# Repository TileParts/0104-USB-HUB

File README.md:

0104-USB-HUB
==========

一个带分控开关的一拖三 USB 2.0 Hub。

## 协议

[CERN-OHL-P-2.0](LICENSE)

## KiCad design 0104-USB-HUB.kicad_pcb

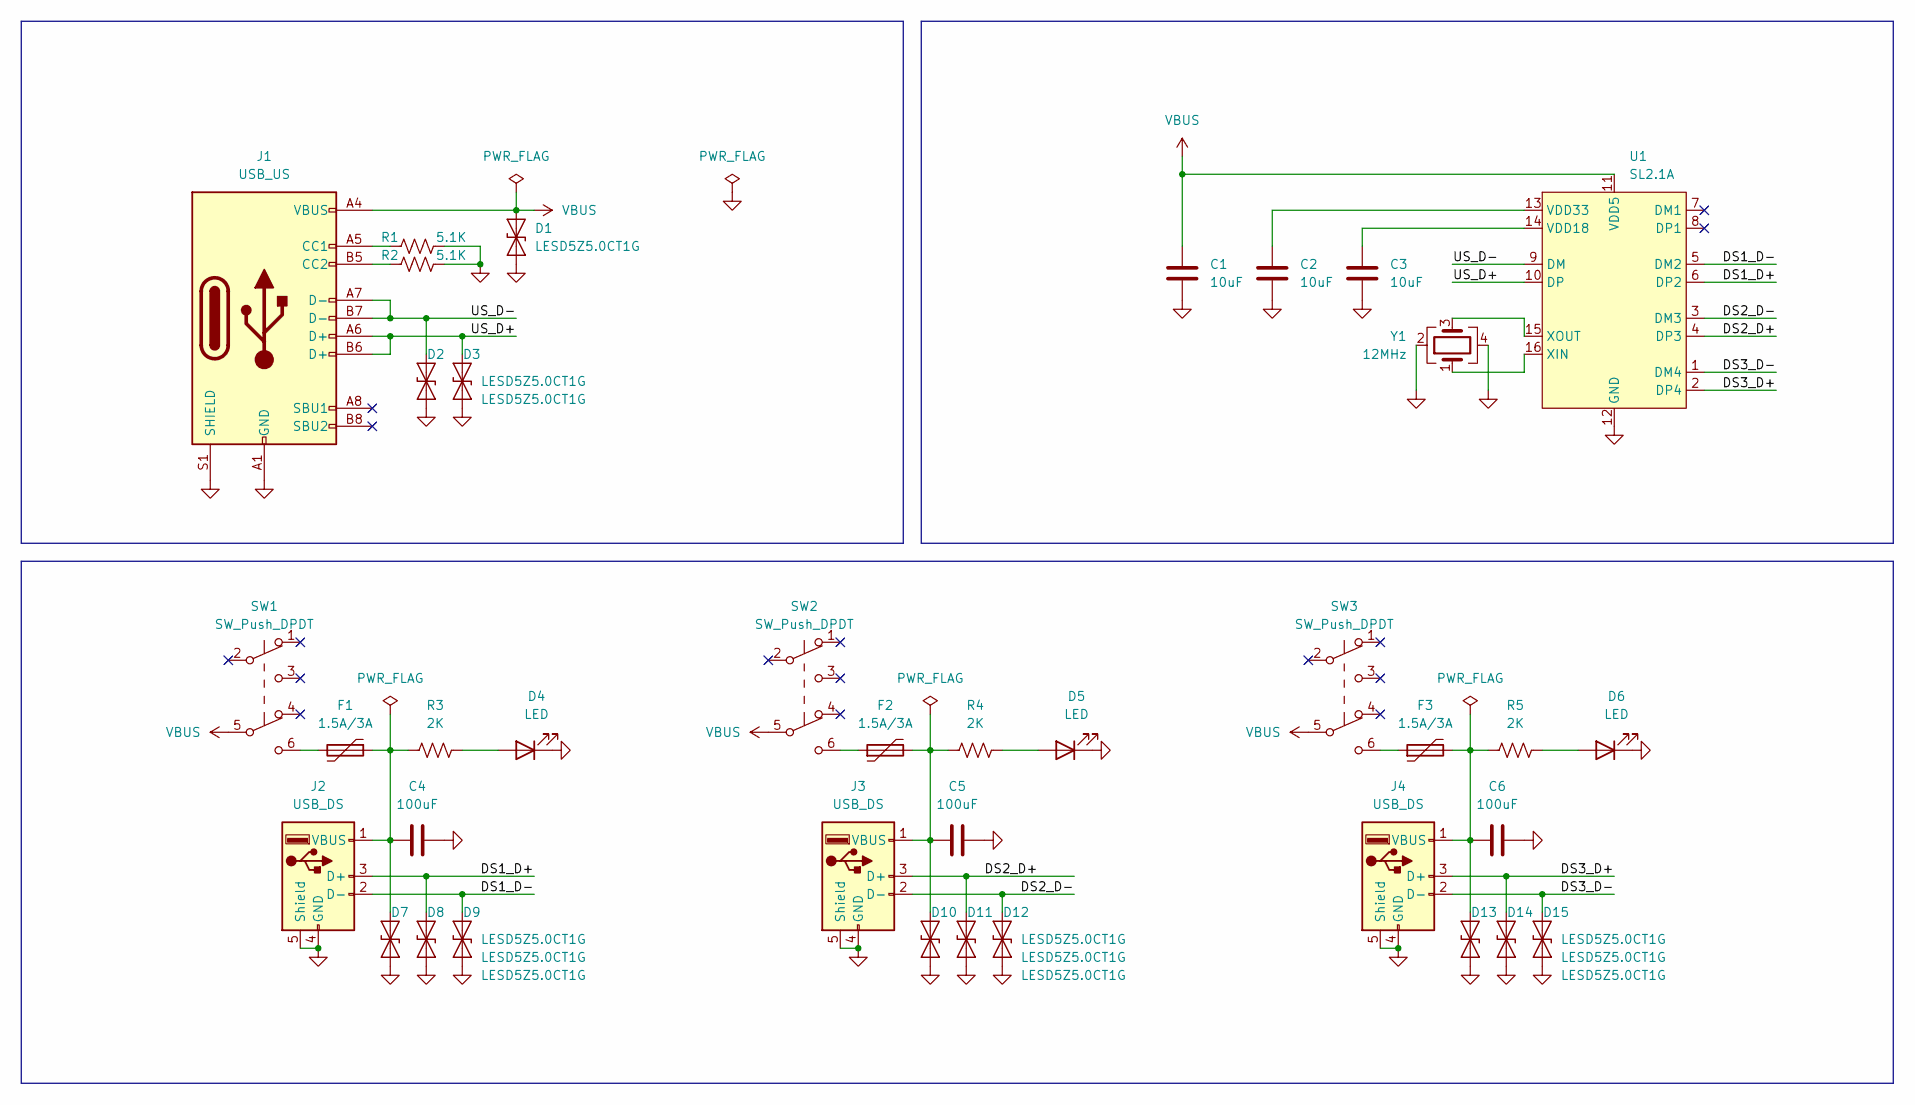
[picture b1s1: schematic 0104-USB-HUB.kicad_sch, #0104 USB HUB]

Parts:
C1: 10uF; C_1206_3216Metric; PartNumber C13585
C2, C3: 10uF; C_0402_1005Metric; PartNumber C15525
C4, C5, C6: 100uF; C_1206_3216Metric; PartNumber C15008
D1, D2, D3, D7, D8, D9, D10, D11, D12, D13, D14, D15: LESD5Z5.0CT1G; D_SOD-523; PartNumber C136167
D4, D5, D6: LED; LED_0603_1608Metric; PartNumber C72041
F1, F2, F3: 1.5A/3A; Fuse_1206_3216Metric; PartNumber C883133
J1: USB_US; HRO_TYPE-C-31-M-12; PartNumber C165948
J2, J3, J4: USB_DS; CKMTW_U-USBAN04P-F005; PartNumber C386739
R1, R2: 5.1K; R_0402_1005Metric; PartNumber C25905
R3, R4, R5: 2K; R_0402_1005Metric; PartNumber C4109
SW1, SW2, SW3: SW_Push_DPDT; SW_Push_DPDT_8.5x8.5mm; PartNumber C194405
U1: SL2.1A; SOP-16_3.9x9.9mm_P1.27mm; PartNumber C192893
Y1: 12MHz; Oscillator_SMD_3.2x2.5mm; PartNumber C9002

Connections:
/DS1_D+: D8.2 (A2), J2.3 (D+), U1.6 (DP2)
/DS1_D-: D9.2 (A2), J2.2 (D-), U1.5 (DM2)
/DS2_D+: D11.2 (A2), J3.3 (D+), U1.4 (DP3)
/DS2_D-: D12.2 (A2), J3.2 (D-), U1.3 (DM3)
/DS3_D+: D14.2 (A2), J4.3 (D+), U1.2 (DP4)
/DS3_D-: D15.2 (A2), J4.2 (D-), U1.1 (DM4)
/US_D+: D3.2 (A2), J1.A6 (D+), J1.B6 (D+), U1.10 (DP)
/US_D-: D2.2 (A2), J1.A7 (D-), J1.B7 (D-), U1.9 (DM)
GND: C1.2, C2.2, C3.2, C4.2, C5.2, C6.2, D1.1 (A1), D2.1 (A1), D3.1 (A1), D4.1 (K), D5.1 (K), D6.1 (K), D7.1 (A1), D8.1 (A1), D9.1 (A1), D10.1 (A1), D11.1 (A1), D12.1 (A1), D13.1 (A1), D14.1 (A1), D15.1 (A1), J1.A1 (GND), J1.A12 (GND), J1.B1 (GND), J1.B12 (GND), J1.S1 (SHIELD), J2.4 (GND), J2.5 (Shield), J3.4 (GND), J3.5 (Shield), J4.4 (GND), J4.5 (Shield), R1.2, R2.2, U1.12 (GND), Y1.2, Y1.4
unnamed: C2.1, U1.13 (VDD33)
unnamed: C3.1, U1.14 (VDD18)
unnamed: C4.1, D7.2 (A2), F1.1, J2.1 (VBUS), R3.1
unnamed: C6.1, D13.2 (A2), F3.2, J4.1 (VBUS), R5.1
unnamed: D4.2 (A), R3.2
unnamed: D5.2 (A), R4.2
unnamed: D6.2 (A), R5.2
unnamed: F1.2, SW1.6 (C)
unnamed: F2.1, SW2.6 (C)
unnamed: C5.1, D10.2 (A2), F2.2, J3.1 (VBUS), R4.1
unnamed: F3.1, SW3.6 (C)
unnamed: J1.A5 (CC1), R1.1
unnamed: J1.B5 (CC2), R2.1
unnamed: U1.15 (XOUT), Y1.3
unnamed: U1.16 (XIN), Y1.1
VBUS: C1.1, D1.2 (A2), J1.A4 (VBUS), J1.A9 (VBUS), J1.B4 (VBUS), J1.B9 (VBUS), SW1.5 (B), SW2.5 (B), SW3.5 (B), U1.11 (VDD5)

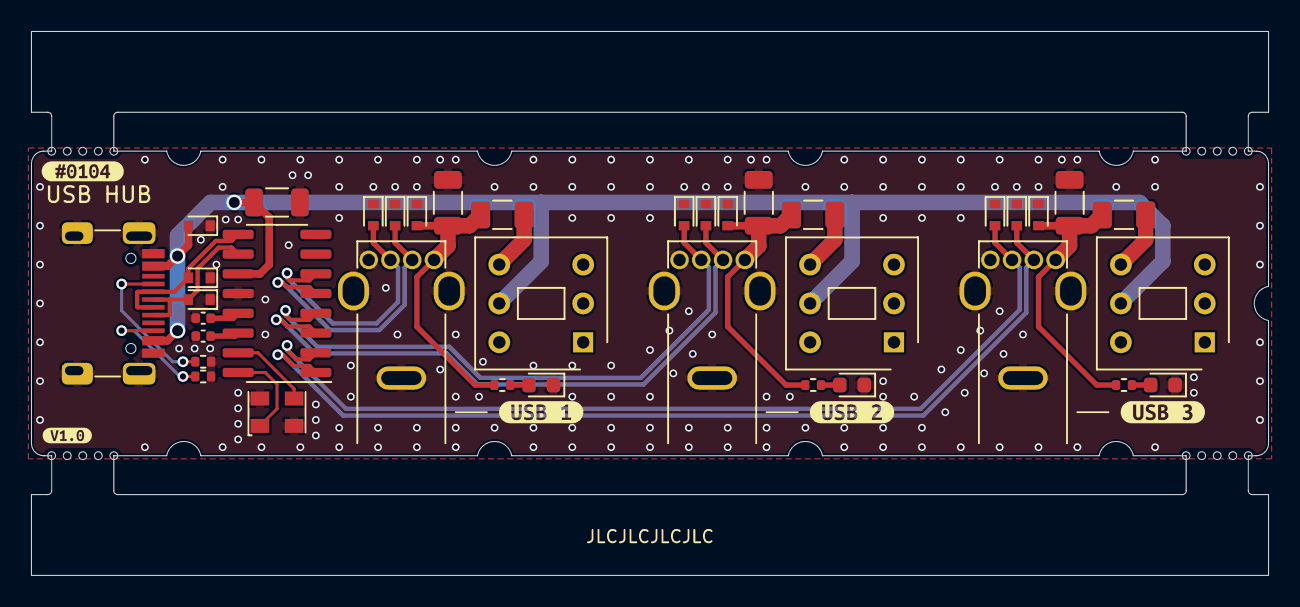
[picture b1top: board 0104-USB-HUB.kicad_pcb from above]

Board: 2 copper layers, 79.6 x 35.0 mm, 43 parts (0 on the bottom side), 25 nets.

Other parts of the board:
kibuzzard-63351CB9: G***; kibuzzard-63351CB9
kibuzzard-63429E4C: G***; kibuzzard-63429E4C
kibuzzard-6343237B: G***; kibuzzard-6343237B
kibuzzard-6343237F: G***; kibuzzard-6343237F
kibuzzard-63432387: G***; kibuzzard-63432387

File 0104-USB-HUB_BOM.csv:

Manufacturer,Comment,Designator,Footprint,Quantity,PartNumber,Supplier
SAMSUNG,10uF,C2 C3,C_0402_1005Metric,2,C15525,JLC
SAMSUNG,10uF,C1,C_1206_3216Metric,1,C13585,JLC
SAMSUNG,100uF,C4 C5 C6,C_1206_3216Metric,3,C15008,JLC
EVERLIGHT,LED,D4 D5 D6,LED_0603_1608Metric,3,C72041,JLC
YXC,12MHz,Y1,Oscillator_SMD_3.2x2.5mm,1,C9002,JLC
UNI-ROYAL,2K,R3 R4 R5,R_0402_1005Metric,3,C4109,JLC
UNI-ROYAL,5.1K,R1 R2,R_0402_1005Metric,2,C25905,JLC
Ckmtw,USB_DS,J2 J3 J4,CKMTW_U-USBAN04P-F005,3,C386739,JLC-EXT
LRC,LESD5Z5.0CT1G,D1 D2 D3 D7 D8 D9 D10 D11 D12 D13 D14 D15,D_SOD-523,12,C136167,JLC-EXT
BHFUSE,1.5A/3A,F1 F2 F3,Fuse_1206_3216Metric,3,C883133,JLC-EXT
HRO,USB_US,J1,HRO_TYPE-C-31-M-12,1,C165948,JLC-EXT
CoreChips,SL2.1A,U1,SOP-16_3.9x9.9mm_P1.27mm,1,C192893,JLC-EXT
GANGYUAN,SW_Push_DPDT,SW1 SW2 SW3,SW_Push_DPDT_8.5x8.5mm,3,C194405,JLC-EXT

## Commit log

2022-10-08 Create repo
2022-10-13 Basic set up
2022-10-13 Finish BOM
2022-10-14 Finish SCH
2022-10-16 Output docs
2022-10-16 Add datasheets
2022-10-16 Output schematic
2022-10-16 Add README
